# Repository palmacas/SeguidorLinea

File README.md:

# SeguidorLinea

Line follower robot based on the PIC16F887, includes five IR sensor for line detection. The code was written for CCS C Compiler.

---
More information:  
[Robot Seguidor de Línea [Spanish]](https://palmacas.com/robot-seguidor-de-linea/)

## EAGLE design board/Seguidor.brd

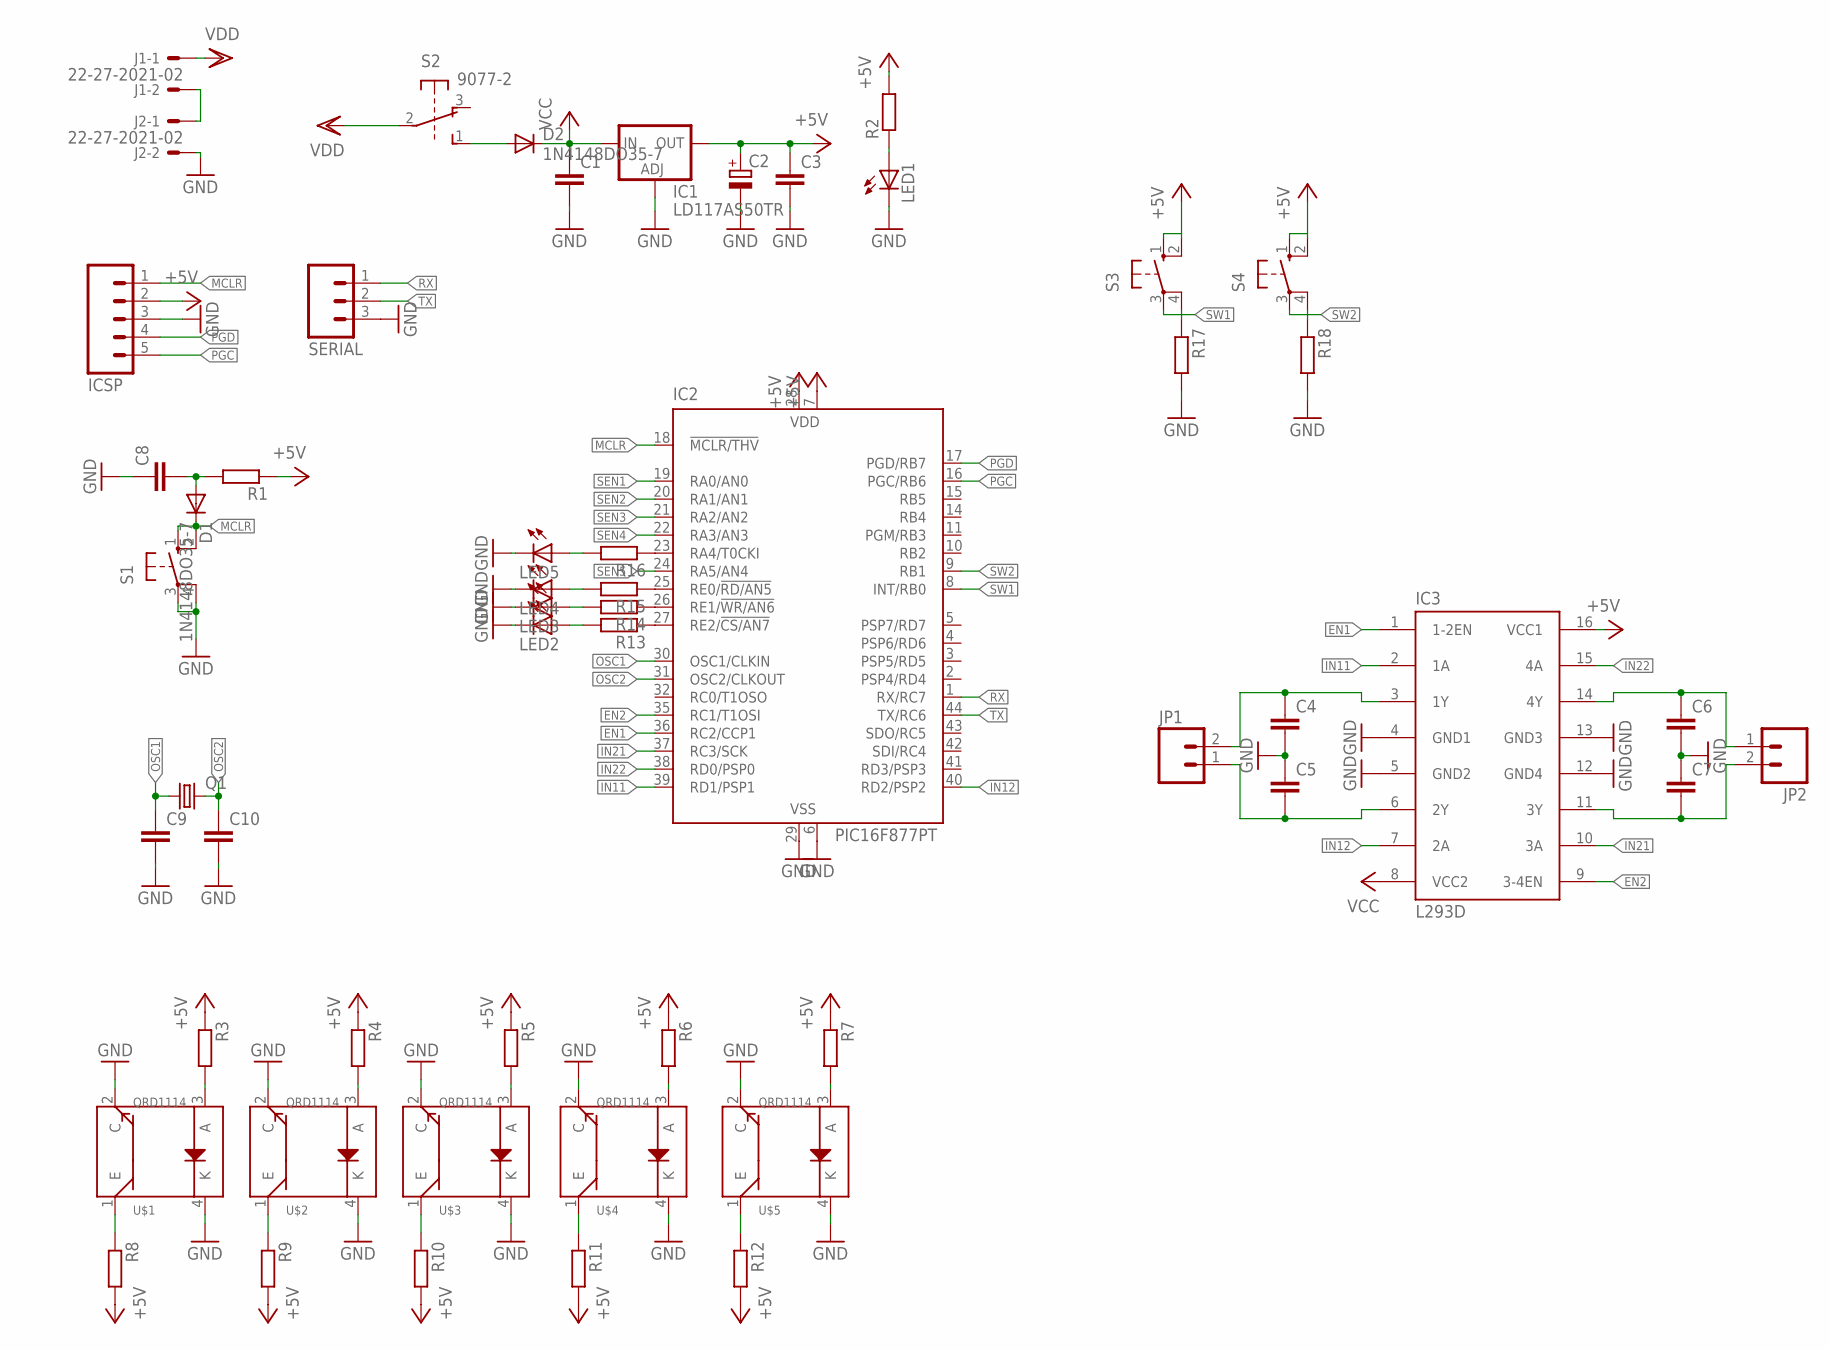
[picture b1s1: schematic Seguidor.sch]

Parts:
C1, C3, C4, C5, C6, C7, C8, C9, C10: C-EU050-024X044; C050-024X044
C2: CPOL-EU153CLV-0405; 153CLV-0405
D1, D2: 1N4148DO35-7; DO35-7
IC1: LD117AS50TR; SOT223
IC2: PIC16F877PT; TQFP44
IC3: L293D; DIL16
ICSP: M05PTH_LONGPADS; 1X05_LONGPADS
J1, J2: 22-27-2021-02; 6410-02
JP1, JP2: M02; 1X02_LONGPADS
LED1, LED2, LED3, LED4, LED5: LED3MM
Q1: CRYSTALHC49UP; HC49UP
R1, R2, R3, R4, R5, R6, R7, R8, R9, R10, R11, R12, R13, R14, R15, R16, R17, R18: R-EU_0207/7; 0207/7
S1: 10-XX; B3F-10XX
S2: 9077-2
S3, S4: 10-XX; B3F-10XX; MPN B3F-1000
SERIAL: M03LOCK_LONGPADS; 1X03_LOCK_LONGPADS
U$1, U$2, U$3, U$4, U$5: QRD1114

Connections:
+5V: C2.+, C3.1, IC1.4 (OUT), IC2.7 (VDD), IC2.28 (VDD), IC3.16 (VCC1), ICSP.2, R1.1, R2.2, R3.1, R4.1, R5.1, R6.1, R7.1, R8.2, R9.2, R10.2, R11.2, R12.2, S3.1 (S), S3.2 (S1), S4.1 (S), S4.2 (S1)
EN1: IC2.36 (RC2/CCP1), IC3.1 (1-2EN)
EN2: IC2.35 (RC1/T1OSI), IC3.9 (3-4EN)
GND: C1.2, C2.-, C3.2, C4.2, C5.1, C6.2, C7.1, C8.1, C9.2, C10.2, IC1.1 (ADJ), IC2.6 (VSS), IC2.29 (VSS), IC3.4 (GND1), IC3.5 (GND2), IC3.12 (GND4), IC3.13 (GND3), ICSP.3, J2.2, LED1.K (C), LED2.K (C), LED3.K (C), LED4.K (C), LED5.K (C), R17.2, R18.2, S1.3, S1.4 (P1), SERIAL.3, U$1.2 (C), U$1.4 (K), U$2.2 (C), U$2.4 (K), U$3.2 (C), U$3.4 (K), U$4.2 (C), U$4.4 (K), U$5.2 (C), U$5.4 (K)
IN11: IC2.39 (RD1/PSP1), IC3.2 (1A)
IN12: IC2.40 (RD2/PSP2), IC3.7 (2A)
IN21: IC2.37 (RC3/SCK), IC3.10 (3A)
IN22: IC2.38 (RD0/PSP0), IC3.15 (4A)
MCLR: D1.C, IC2.18 (!MCLR/THV), ICSP.1, S1.1 (S), S1.2 (S1)
unnamed: J1.2, J2.1
unnamed: LED1.A, R2.1
unnamed: C6.1, IC3.14 (4Y), JP2.1
unnamed: C4.1, IC3.3 (1Y), JP1.2
unnamed: C5.2, IC3.6 (2Y), JP1.1
unnamed: C7.2, IC3.11 (3Y), JP2.2
unnamed: D2.A, S2.1 (S)
unnamed: C8.2, D1.A, R1.2
unnamed: R3.2, U$1.3 (A)
unnamed: R4.2, U$2.3 (A)
unnamed: R5.2, U$3.3 (A)
unnamed: R6.2, U$4.3 (A)
unnamed: R7.2, U$5.3 (A)
unnamed: IC2.27 (RE2/!CS/AN7), R13.1
unnamed: IC2.26 (RE1/!WR/AN6), R14.1
unnamed: IC2.25 (RE0/!RD/AN5), R15.1
unnamed: IC2.23 (RA4/T0CKI), R16.1
unnamed: LED3.A, R14.2
unnamed: LED2.A, R13.2
unnamed: LED4.A, R15.2
unnamed: LED5.A, R16.2
OSC1: C9.1, IC2.30 (OSC1/CLKIN), Q1.1
OSC2: C10.1, IC2.31 (OSC2/CLKOUT), Q1.2
PGC: IC2.16 (PGC/RB6), ICSP.5
PGD: IC2.17 (PGD/RB7), ICSP.4
RX: IC2.1 (RX/RC7), SERIAL.1
SEN1: IC2.19 (RA0/AN0), R8.1, U$1.1 (E)
SEN2: IC2.20 (RA1/AN1), R9.1, U$2.1 (E)
SEN3: IC2.21 (RA2/AN2), R10.1, U$3.1 (E)
SEN4: IC2.22 (RA3/AN3), R11.1, U$4.1 (E)
SEN5: IC2.24 (RA5/AN4), R12.1, U$5.1 (E)
SW1: IC2.8 (INT/RB0), R17.1, S3.3, S3.4 (P1)
SW2: IC2.9 (RB1), R18.1, S4.3, S4.4 (P1)
TX: IC2.44 (TX/RC6), SERIAL.2
VCC: C1.1, D2.C, IC1.3 (IN), IC3.8 (VCC2)
VDD: J1.1, S2.2

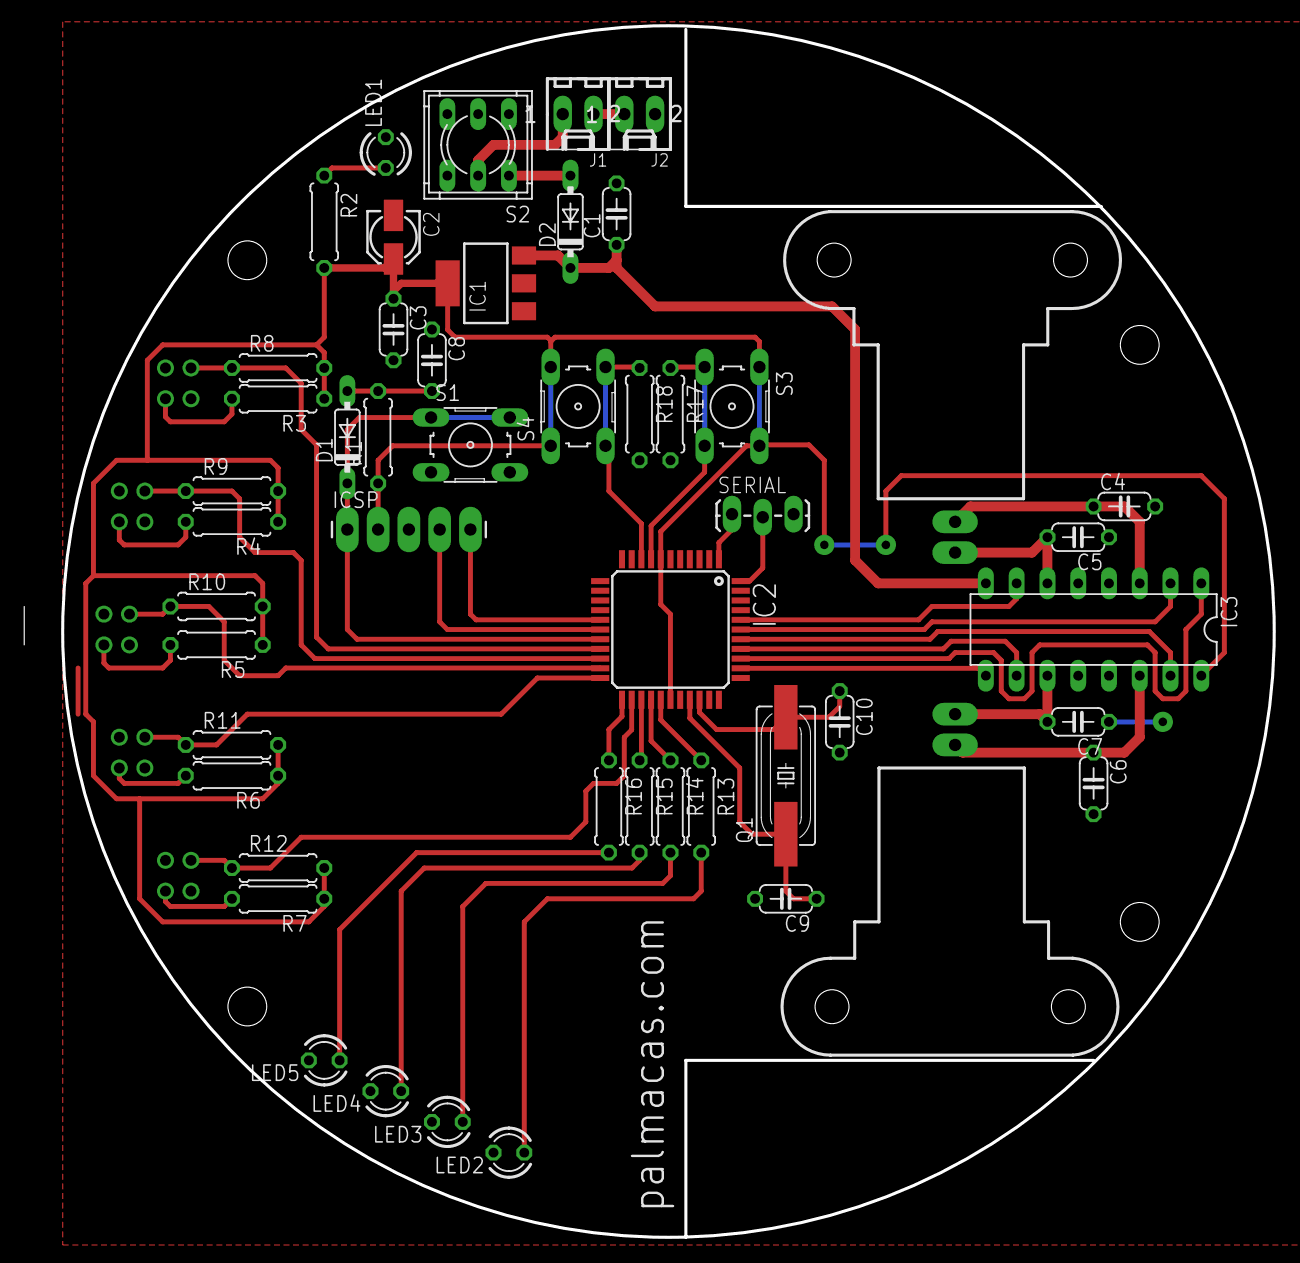
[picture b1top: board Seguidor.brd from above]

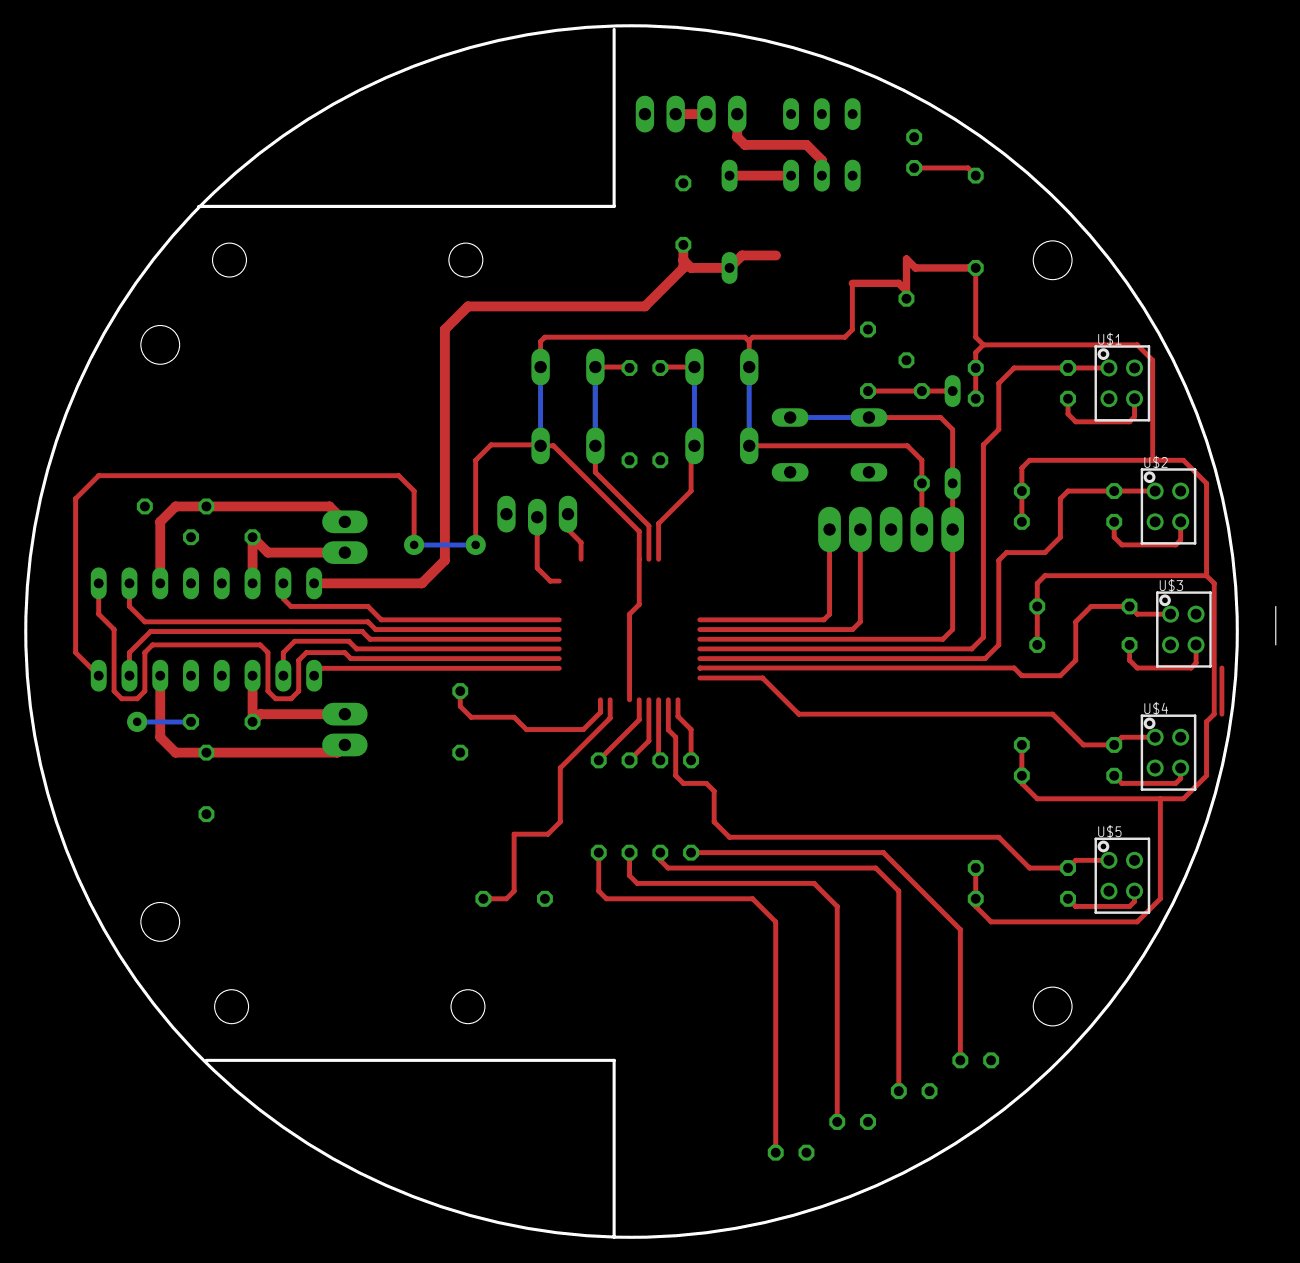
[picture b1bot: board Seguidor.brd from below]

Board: 2 copper layers, 103.0 x 100.0 mm, 56 parts (5 on the bottom side), 45 nets.

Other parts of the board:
U$6, U$7: MINI_MOTOR

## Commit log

2020-06-02 Board update
2020-06-02 Code update
2020-06-02 Update LICENSE
2020-06-03 Addition .hex

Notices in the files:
parts and their libraries:
SparkFun: Licensing: CC v3.0 Share-Alike You are welcome to use this library for commercial purposes.
